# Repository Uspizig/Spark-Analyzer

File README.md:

# Spark Analyzer: The Programmable USB-C Power Delivery Analyzer & Power Supply

This is a modification of Spark Analyser to my personal needs. Please check the original Product here [now](https://www.crowdsupply.com/elektrothing/spark-analyzer).

The **Spark Analyzer** excels in power management. It is a versatile ESP32-powered device tailored for enhancing project development and debugging processes. It is fully compatible with USB-C Power Delivery (PD) and also supports the Programmable Power Supply (PPS) feature, allowing for precise control and management of power. Its compact design facilitates easy inline integration with existing setups, providing essential insights and control over power delivery.

Equipped with WiFi and BLE, the Spark Analyzer offers wireless connectivity, enabling developers to remotely monitor and adjust voltage levels, log data, and analyze power consumption through a user-friendly interface. This design prioritizes convenience and efficiency, removing the need for physical buttons and supporting distance operation.

## Features:

1. **Configure USB Power Delivery PD**: When the Spark Analyzer is connected to a USB port that supports Power Delivery (PD), you can configure the output voltage as 5V, 9V, 15V or 20V.

2. **Configure USB Programmable Power Supply PPS**: When the Spark Analyzer is connected to a USB port that supports Programmable Power Supply (PPS), then you can configure the output voltage between 3.3V and 21V in steps of 20 mV. You can also limit the current up to 3A in steps of 50mA.

3. **Power Analysis**: The Spark Analyzer comes with a current sensor. This allows for accurate current draw measurements, essential for understanding power usage in your projects.

4. **Wireless Control**: Untehther your development process with the Spark Analyzer’s wireless capabilities. With both WiFi and BLE, this tool allows remote control and data logging. Users can adjust settings and monitor data from a distance, offering a more flexible development experience.

5. **Open Source & Programmable**: As an open-source device, the Spark Analyzer offers unmatched versatility. It is fully programmable, allowing you to tailor its functionality to your specific applications. This customization extends to software and hardware, opening up endless possibilities for creative and efficient project development.

6. **Compact Design**: Designed for convenience, the Spark Analyzer's compact and sleek form factor allows for seamless integration into existing setups. Its compatibility with USB PD power sources and inline integration capability minimizes the need for additional equipment or extensive redesign, making it a versatile and user-friendly addition to any development environment.

5. **Safety**: Safety is crucial when working with electricity and is at the heart of Spark Analyzer. An integrated output FET allows for software programmable current limit that switches off the power in high-current scenarios.

6. **Data Storage**: Store your Voltage Curves on SD Card and play back voltage ramps

7. **Display**: Monitor live the current status of the Voltage Source

8. **RTC**: Operate the Device in remote areas without Wifi in Standalone mode and still have a proper Time Monitoring

9. **Air Quality**: Measure the Air Qulity with the BME680, BME688 or BME690: Temperature, Humidity, Pressure and eCO² to take actions based on Enviromental Data

10. **Gyro, ACC**: Identify Movement of the Device and take actions.

## Specifications

#### Power
- **Negotiable Power Delivery**: Options of 5 VDC, 9 VDC, 12 VDC, 15 VDC, 20 VDC; max 5 A (100 W at 20 VDC). It is also PPS compatible up to 21 VDC. Note: the Spark Analyzer comes preinstalled with firmware that supports PD. If you want to use PPS you can load this version instead: [WebApp_PPS](https://github.com/tooyipjee/Spark-Analyzer/tree/master/PlatformIO/WebApp_PPS).
- **USB Type-C Port**: For power delivery and integrated JTAG programming.
- **ON Semiconductor [FUSB302MPX](https://www.onsemi.com/pdf/datasheet/fusb302b-d.pdf)**: Programmable USB Type-C control and USB PD communication.
- **ESD Protection**: On D+/D-/CC1/CC2 pins.
- **Texas Instruments [TPS62175DQCT](https://www.ti.com/product/TPS62175/part-details/TPS62175DQCT)**: 3.3 VDC 0.5 A max output DC-DC Step-Down Converter.
- **Power Output**: 3.5 mm, 2-position terminal block.

#### I/O Configuration
- **GPIOs**: 4 GPIOs (I2C, UART, SPI compatible).
- **Power Pins**: 1x 5 VDC and 1x GND.

#### Microcontroller
- **Model**: [ESP32-S3 Wroom](https://www.espressif.com/sites/default/files/documentation/esp32-s3-wroom-1_wroom-1u_datasheet_en.pdf) 
- **Wi-Fi**: 802.11b/g/n.
- **Bluetooth**: BLE 4.2.
- **Flash Memory**: 4 MB.

#### Interface
- **3x LED Indicators**
  - Power On
  - Output Enable
  - Programmable LED/Debug
  - 2 x WS2812-4020 RGB Edge LED
- **Display**
  - GCA9a01 240x240 round Display
  - Backlight can be operated seperatly
- **Buttons**
  - Reset
  - Programmable 2Buttons/Debug
  - Jog Dial
- **Sensors**
  - LSM6 Gyro
  - RV3028 RTC Ultra Low Power
  - 4 GPIOs(3V3 logic) for operating outputs or read out Tacho Signals of FANs
  - BME280 (optional)
  - BME680 (optional) or - BME688 (optional) or - BME690 (optional)
- **Audio Amplifier**
  - MAX983657 AMP for Loudspeaker

#### Programming
- **RX/TX Pins**: For programming.
- **Micro SD Card**: For recall configuration files.
- **USB-C**: Built-in USB JTAG programmer (ESP32-S3), compatible with Arduino. Select ESP32-S3 Dev Board.

#### Output
- **Current Output**: [CC6904SO-10A](https://datasheet.lcsc.com/lcsc/2304140030_Cross-chip-CC6904SO-10A_C469389.pdf).
- **Current Sensor**: Hall Effect Current Sensor.
- **Output Enable**: [DMP3017SFG-7 FET](https://www.diodes.com/assets/Datasheets/products_inactive_data/DMP3017SFG.pdf).

## Spark Analyzer Mobile App

> **Note**: The Spark Analyzer Mobile App is currently in active development. The features described below are subject to change as we continue to improve the app.

The Spark Analyzer Mobile App, currently done for [Android](https://play.google.com/store/apps/details?id=com.elektrothing.SparkAnalyzer&hl=en&gl=US) (iOS support is available via [RemoteXY](https://apps.apple.com/us/app/remotexy/id1168130280), is the perfect companion to your Spark Analyzer device. It simplifies monitoring and controlling power delivery with these key features:

- **Voltage Selector**: Easily choose from different voltage levels (5 VDC, 9 VDC, 15 VDC, or 20 VDC) using a user-friendly selector.
- **Output Toggle**: Turn the power output on or off conveniently with a toggle switch.
- **Current Logging**: Save current draw as a .csv file.
- **Current Limit**: Ability to set a software current trip as a safety feature.
- **Read-time Display**: View current set point, current draw and output enable in real time on your phone.

### Key Features:

- **Voltage Selector**: The app comes with a user-friendly voltage selector that allows you to easily choose from the different voltage levels supported by the UCPD protocol. Whether you need 5V, 9V, 15V, or 20V, switching between these options is just a tap away.

- **Output Toggle**: Need to turn the power output on or off? The app features a convenient toggle switch that gives you full control over the Spark Analyzer's output, making it simple to manage your device remotely.

- **Current Draw Chart**: Keep an eye on your project's power consumption with the app's real-time current draw chart. This feature provides a graphical representation of the current being drawn, helping you to monitor and optimize your power usage effectively.

### Future Developments:

The Spark Analyzer Mobile App is continuously being improved, with several new features in the pipeline. Upcoming updates will include the ability to export logs for further analysis, set current limits to prevent overcurrent scenarios, and much more.

## Testing for Performance

At the heart of Spark Analyzer's design is a commitment to reliability and performance. To ensure that Spark Analyzer stands up to real-world demands, we subjected it to testing under use conditions.

### Max Current Test: 3A at 9V
Under a load condition of 3A at 9V, Spark Analyzer showcased its robust power delivery capabilities without any hitches.

### Max Voltage Test: 1.5A at 20V
Even at its maximum voltage output of 20V with a 1.5A load, Spark Analyzer continued to perform seamlessly, demonstrating its versatility and reliability.

## License

MIT License

Copyright (c) 2023 elektroThing

Permission is hereby granted, free of charge, to any person obtaining a copy
of this software and associated documentation files (the "Software"), to deal
in the Software without restriction, including without limitation the rights
to use, copy, modify, merge, publish, distribute, sublicense, and/or sell
copies of the Software, and to permit persons to whom the Software is
furnished to do so, subject to the following conditions:

The above copyright notice and this permission notice shall be included in all
copies or substantial portions of the Software.

THE SOFTWARE IS PROVIDED "AS IS", WITHOUT WARRANTY OF ANY KIND, EXPRESS OR
IMPLIED, INCLUDING BUT NOT LIMITED TO THE WARRANTIES OF MERCHANTABILITY,
FITNESS FOR A PARTICULAR PURPOSE AND NONINFRINGEMENT. IN NO EVENT SHALL THE
AUTHORS OR COPYRIGHT HOLDERS BE LIABLE FOR ANY CLAIM, DAMAGES OR OTHER
LIABILITY, WHETHER IN AN ACTION OF CONTRACT, TORT OR OTHERWISE, ARISING FROM,
OUT OF OR IN CONNECTION WITH THE SOFTWARE OR THE USE OR OTHER DEALINGS IN THE
SOFTWARE.

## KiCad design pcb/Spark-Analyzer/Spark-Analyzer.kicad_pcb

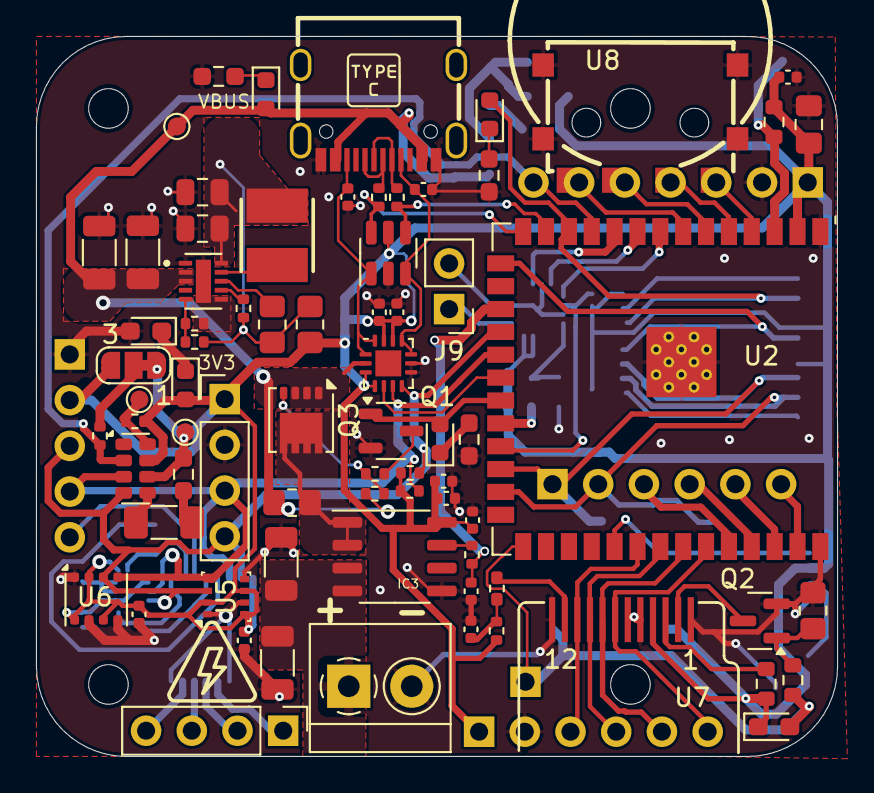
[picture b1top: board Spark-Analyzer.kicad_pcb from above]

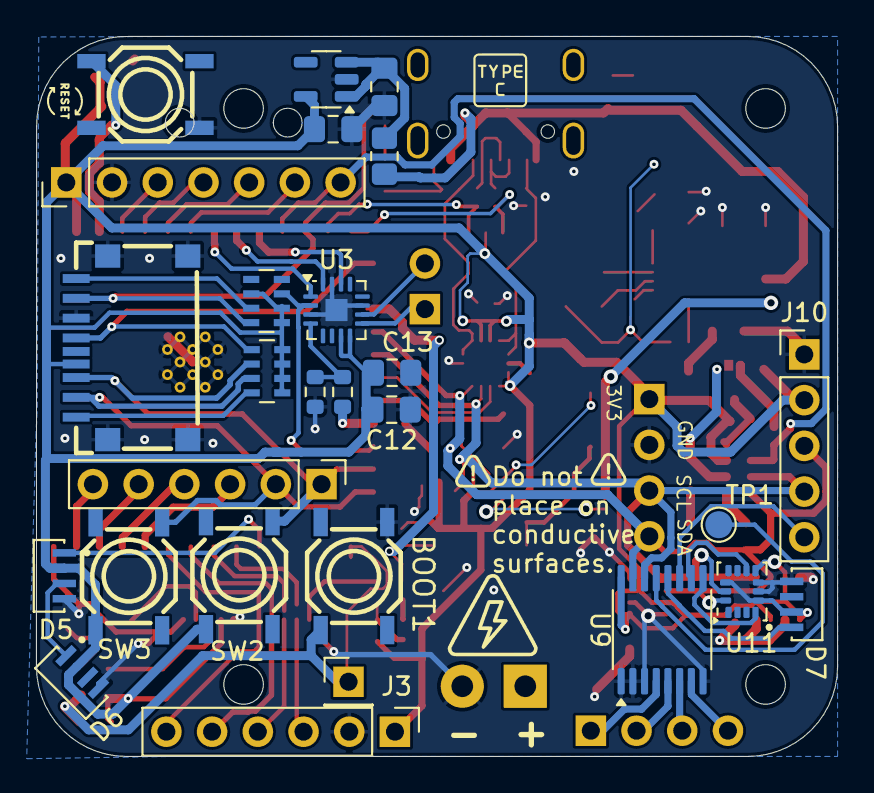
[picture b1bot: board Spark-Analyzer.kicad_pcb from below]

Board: 4 copper layers, 44.5 x 40.0 mm, 107 parts (28 on the bottom side), 78 nets.

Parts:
 : LOGO; highVoltage
 #2: LOGO; highVoltage
BOOT1: SW_Push; SW-SMD_4P-CORR-L5.2-W5.2-P3.70-LS6.4
C1, C20, C21, C22: 10u_1206; C_1206_3216Metric
C2: 22u; C_0805_2012Metric
C3: 10u; C_0805_2012Metric
C4, C5: 100p; C_0402_1005Metric
C6, C7, C8, C9, C11, C14, C15, C16, C24, C25: 100nF; C_0402_1005Metric
C10, C12, C13: 1uF; C_0805_2012Metric_Pad1.18x1.45mm_HandSolder
C17, C18: 4.7uF50V; C_0805_2012Metric_Pad1.18x1.45mm_HandSolder
C19: 220uF; C_1206_3216Metric_Pad1.33x1.80mm_HandSolder
D1, D2, D4: Green_0603; LED_0603_1608Metric
D3: Yellow_0603; LED_0603_1608Metric
D5, D6, D7: WS2812B-4020; LED_WS2812B-4020
H1, H2, H3, H4: MountingHole; MountingHole_2.2mm_M2
IC2: FUSB302MPX; WQFN-14-1EP_2.5x2.5mm_P0.5mm_EP1.45x1.45mm
IC3: CC6904SO-10A; SOP-8_3.9x4.9mm_P1.27mm
IC4: TPS62175DQCT; SON50P300X200X80-11N
J1: GT-USB-7010; USB-C_SMD-TYPE-C-31-M-12
J3, J12: Conn_01x06_Pin; PinHeader_1x06_P2.54mm_Vertical
J4, J7: Conn_01x04; PinHeader_1x04_P2.54mm_Vertical
J5: Conn_01x01; PinHeader_1x01_P2.54mm_Vertical
J6: Micro_SD_Card_Det_US; TF-SMD_XKTF-0803-0
J8: Conn_01x07_Pin; PinHeader_1x07_P2.54mm_Vertical
J9: Conn_01x02_Pin; PinHeader_1x02_P2.54mm_Vertical
J10: Conn_01x05; PinHeader_1x05_P2.54mm_Vertical
J11: KF350-3.5-2P; TerminalBlock_4Ucon_1x02_P3.50mm_Horizontal
JP1: SolderJumper_3_Bridged12; SolderJumper-3_P1.3mm_Bridged12_RoundedPad1.0x1.5mm_NumberL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
L1: 10uH; INDPM4040X300N
Q1: DTC143ECA-TP; SOT-23-3
Q2: 2N7002; SOT-23
Q3: DMP3017SFG-7; Diodes_PowerDI3333-8
R1: 100k; R_0402_1005Metric
R2: 1M2; R_0402_1005Metric
R3: 383k; R_0402_1005Metric
R4, R5: 0; R_0805_2012Metric_Pad1.20x1.40mm_HandSolder
R6, R7: 22; R_0402_1005Metric
R8: 100; R_0402_1005Metric
R9, R16: 2.7k; LED_0603_1608Metric_Pad1.05x0.95mm_HandSolder
R10, R12: 10k; R_0603_1608Metric
R11: 1M; R_0805_2012Metric_Pad1.20x1.40mm_HandSolder
R13, R14, R19, R24: 10k; R_0402_1005Metric
R15: 0R; R_0402_1005Metric_Pad0.72x0.64mm_HandSolder
R17, R18, R22: 2.7k; R_0603_1608Metric_Pad0.98x0.95mm_HandSolder
R20: 1k; R_0402_1005Metric
R21: DNF_0805; R_0805_2012Metric_Pad1.20x1.40mm_HandSolder
R23: 22; R_0603_1608Metric
R25: N.C.; R_0603_1608Metric
R26: 300K; R_0603_1608Metric
R27, R29: 10K; R_0402_1005Metric
R28: 0R; R_0805_2012Metric_Pad1.20x1.40mm_HandSolder
R30: 300R; R_0603_1608Metric_Pad0.98x0.95mm_HandSolder
RES1: SW_Push; SW-SMD_4P-CORR-L5.2-W5.2-P3.70-LS6.4
RN2, RN3: R_Pack04_Split; R_Array_Concave_4x0603
SW2, SW3: SW_Push; SW-SMD_4P-CORR-L5.2-W5.2-P3.70-LS6.4
TP1: TestPoint; TestPoint_Pad_D1.5mm
TP2, TP3, TP4: TestPoint; TestPoint_Pad_D1.0mm
U1: SRV05-4; SOT-23-6
U2: ESP32-S3-WROOM-1
U3: MAX98357A; TQFN-16-1EP_3x3mm_P0.5mm_EP1.23x1.23mm
U4: RV3032; MicroCrystal_C7_SON-8_1.5x3.2mm_P0.9mm
U5: BME280; Bosch_LGA-8_2.5x2.5mm_P0.65mm_ClockwisePinNumbering
U6: BME680; Bosch_LGA-8_3x3mm_P0.8mm_ClockwisePinNumbering
U7: GC9A01_IPS_display; GC9A01_IPS_display_reversed
U8: SIQ-02FVS3; SW-SMD_SIQ-02FVS3_1
U9: TCA9554PW; TSSOP-16_4.4x5mm_P0.65mm
U10: RT9013; SOT-23-5
U11: LSM6DSL; LGA-14_3x2.5mm_P0.5mm_LayoutBorder3x4y

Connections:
+3V3: C6.2, C7.1, C9.1, C10.1, C12.2, C13.1, C14.2, C15.1, C16.1, C18.2, C24.2, C25.2, D1.2 (A), D5.2 (VDD), D6.2 (VDD), D7.2 (VDD), IC2.3 (VDD_1), IC2.4 (VDD_2), IC2.12 (VCONN_1), IC2.13 (VCONN_2), IC3.8 (VCC), J3.1, J6.4 (VDD), J7.1, J8.1, J10.2, JP1.3 (B), R4.2, R9.1, R12.1, R13.1, R14.1, R23.1, R24.1, R29.2, RN2.1 (R1.1), RN2.2 (R2.1), RN2.6 (R3.2), RN3.5 (R4.2), RN3.6 (R3.2), RN3.7 (R2.2), RN3.8 (R1.2), SW2.2, SW3.2, U1.5 (VP), U2.2 (3V3), U3.7 (VDD), U3.8 (VDD), U4.7 (VDD), U5.2 (CSB), U5.6 (VDDIO), U5.8 (VDD), U6.2 (CSB), U6.6 (VDDIO), U6.8 (VDD), U7.4 (VDD), U9.16 (VDD), U10.5 (VOUT), U11.5 (VDDIO), U11.8 (VDD), U11.12 (CS)
/Current Sensor + Output Control/BSST: IC3.1 (IP+), IC3.2 (IP+), Q3.5 (D_1), R21.2
/Current Sensor + Output Control/OUTPUT_EN: D3.2 (A), Q1.1, U2.21 (GPIO13/TOUCH13/ADC2_CH2/FSPIQ/FSPIIO7/S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)
/Current Sensor + Output Control/VOUT: C1.1, C22.1, IC3.3 (IP-), IC3.4 (IP-), J11.1
/Current Sensor + Output Control/V_CURRENT: C8.1, R8.2, U2.17 (GPIO9/TOUCH9/ADC1_CH8/FSPIHD/SUBSPIHD)
/Microcontroller/AUDIO_CLK: U2.9 (GPIO16/U0CTS/ADC2_CH5/XTAL_32K_NH5), U3.16 (BCLK)
/Microcontroller/AUDIO_DAT: U2.8 (GPIO15/U0RTS/ADC2_CH4/XTAL_32K_P), U3.1 (DIN)
/Microcontroller/AUDIO_GAIN: RN2.3 (R3.1), U2.23 (GPIO21), U3.2 (GAIN_SLOT)
/Microcontroller/AUDIO_LR: U2.10 (GPIO17/U1TXD/ADC2_CH6), U3.14 (LRCLK)
/Microcontroller/AUDIO_SD: R26.2, U2.22 (GPIO14/TOUCH14/ADC2_CH3/FSPIWP/FSPIDQS/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)
/Microcontroller/BLK: BOOT1.2, J5.1, R9.2, R10.2, U2.27 (GPIO0/BOOT)
/Microcontroller/CMD: J6.3 (CMD), J12.1, RN3.2 (R2.1), SW2.1, U2.24 (GPIO47/SPICLK_P/SUBSPICLK_P_DIFF)
/Microcontroller/DAT0: D4.2 (A), J6.7 (DAT0), RN2.8 (R1.2), U2.12 (GPIO8/TOUCH8/ADC1_CH7/SUBSPICS1)
/Microcontroller/DAT1: J6.8 (DAT1), RN2.7 (R2.2)
/Microcontroller/DAT3: J6.2 (DAT3/CD), J12.2, RN3.3 (R3.1), SW3.1, U2.25 (GPIO48/SPICLK_N/SUBSPICLK_N_DIFF)
/Microcontroller/EN: R12.2, RES1.1, U2.3 (EN)
/Microcontroller/GPIO1: J12.6, U2.39 (GPIO1/TOUCH1/ADC1_CH0)
/Microcontroller/GPIO2: J12.5, U2.38 (GPIO2/TOUCH2/ADC1_CH1)
/Microcontroller/GPIO4: J8.3, U2.4 (GPIO4/TOUCH4/ADC1_CH3), U8.B
/Microcontroller/GPIO5: J8.4, U2.5 (GPIO5/TOUCH5/ADC1_CH4), U8.C
/Microcontroller/GPIO6: J8.5, U2.6 (GPIO6/TOUCH6/ADC1_CH5), U8.S
/Microcontroller/GPIO7: J8.6, U2.7 (GPIO7/TOUCH7/ADC1_CH6), U8.A
/Microcontroller/GPIO38: D5.1 (DIN), U2.31 (GPIO38/FSPIWP/SUBSPIWP)
/Microcontroller/INT1: U9.9 (P4), U11.4 (INT1)
/Microcontroller/INT2: U9.10 (P5), U11.9 (INT2)
/Microcontroller/INT_N: IC2.5 (INT_N), U2.20 (GPIO12/TOUCH11/ADC2_CH0/FSPICS0/FSPIIO4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)
/Microcontroller/LEDK: Q2.3 (D), U7.2 (LEDK)
/Microcontroller/LED_DIS: R23.2, U7.3 (LEDA)
/Microcontroller/MOSI: J3.3, U2.32 (MTCK/GPIO39/CLK_OUT3/SUBSPICS1), U7.10 (SDI)
/Microcontroller/RES_DIS: R15.1, U7.11 (~RESET)
/Microcontroller/RV3028_Int: J8.7, R27.2, U2.11 (GPIO18/U1RXD/ADC2_CH7/CLK_OUT3), U4.2 (INT)
/Microcontroller/SCK: J3.4, U2.33 (MTDO/GPIO40/CLK_OUT2), U7.9 (SCK)
/Microcontroller/SCL: IC2.6 (SCL), J7.3, J10.4, R14.2, U2.19 (GPIO11/TOUCH11/ADC2_CH0/FSPICS0/FSPIIO4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), U4.3 (SCL), U5.4 (SCK), U6.4 (SCK), U9.14 (SCL), U11.13 (SCL)
/Microcontroller/SDA: IC2.7 (SDA), J7.4, J10.3, R13.2, U2.18 (GPIO10/TOUCH10/ADC1_CH9/FSPICS0/FSPIIO4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), U4.4 (SDA), U5.3 (SDI), U6.3 (SDI), U9.15 (SDA), U11.14 (SDA)
/Microcontroller/SDCK: J6.5 (CLK), RN3.1 (R1.1), U2.15 (GPIO3/TOUCH3/ADC1_CH2)
/Microcontroller/SQW: J10.5, U9.11 (P6)
/Microcontroller/TFT_CS: J3.5, U2.34 (MTDI/GPIO41/CLK_OUT1), U7.8 (~CS)
/Microcontroller/TFT_DC: J3.6, U2.35 (MTMS/GPIO42), U7.7 (D/C)
/Microcontroller/U0RXD: J12.3, U2.36 (U0RXD/GPIO44/CLK_OUT2)
/Microcontroller/U0TXD: J12.4, U2.37 (U0TXD/GPIO43/CLK_OUT1)
/Microcontroller/USB_DN: R6.2, U1.4 (IO3), U2.13 (GPIO19/U1RTS/ADC2_CH8/CLK_OUT2/USB_D-)
/Microcontroller/USB_DP: R7.1, U1.6 (IO4), U2.14 (GPIO20/U1CTS/ADC2_CH9/CLK_OUT1/USB_D+)
GND: BOOT1.1, C1.2, C2.2, C3.2, C4.2, C5.2, C6.1, C7.2, C8.2, C9.2, C10.2, C11.2, C12.1, C13.2, C14.1, C15.2, C16.2, C17.1, C18.1, C19.2, C20.2, C21.2, C22.2, C24.1, C25.1, D5.4 (VSS), D6.4 (VSS), D7.4 (VSS), IC2.8 (GND_1), IC2.9 (GND_2), IC3.5 (GND), IC4.1 (PGND), IC4.6 (AGND), IC4.11 (EP), J1.A1 (GND), J1.A12 (GND), J1.B1 (GND), J1.B12 (GND), J3.2, J6.6 (VSS), J6.10 (SHELL), J6.11 (SHELL), J6.12 (SHELL), J6.13 (SHELL), J7.2, J8.2, J10.1, J11.2, Q1.2, Q2.2 (S), R3.2, R11.1, R16.2, R17.2, R18.2, R22.2, R25.1, RES1.2, U1.2 (VN), U2.1 (GND), U2.40 (GND), U2.41 (GND), U3.3 (GND), U3.11 (GND), U3.15 (GND), U3.17 (PAD), U4.5 (GND), U5.1 (GND), U5.5 (SDO), U5.7 (GND), U6.1 (GND), U6.5 (SDO), U6.7 (GND), U7.1 (GND), U7.5 (GND), U7.6 (GND), U7.12 (GND), U8.1 (EH), U8.2 (EH), U8.5 (EH), U8.6 (EH), U9.1 (A0), U9.2 (A1), U9.3 (A2), U9.8 (GND), U10.2 (GND), U11.6 (GND), U11.7 (GND)
unnamed: C11.1, R15.2, R24.2
unnamed: C19.1, R30.1
unnamed: D1.1 (K), R16.1
unnamed: D2.1 (K), R17.1
unnamed: D3.1 (K), R18.1
unnamed: D4.1 (K), R22.1
unnamed: D5.3 (DOUT), D6.1 (DIN)
unnamed: D7.1 (DIN), U9.12 (P7)
unnamed: C5.1, IC2.10 (CC1_1), IC2.11 (CC1_2), J1.A5 (CC1), U1.3 (IO2)
unnamed: C4.1, IC2.1 (CC2_1), IC2.14 (CC2_2), J1.B5 (CC2), U1.1 (IO1)
unnamed: IC3.7 (OUT), R8.1
unnamed: IC4.5 (FB), R2.2, R3.1
unnamed: IC4.7 (PG), R1.2
unnamed: IC4.8 (SLEEP), R5.1
unnamed: IC4.9 (SW), L1.1
unnamed: C2.1, C3.1, IC4.10 (VOS), L1.2, R1.1, R2.1, R4.1, R5.2
unnamed: J1.A6 (D+), J1.B6 (D+), R7.2
unnamed: J1.A7 (D-), J1.B7 (D-), R6.1
unnamed: J4.1, U9.4 (P0)
unnamed: J4.2, U9.5 (P1)
unnamed: J4.3, U9.6 (P2)
unnamed: J4.4, U9.7 (P3)
unnamed: J6.1 (DAT2), RN3.4 (R4.1)
unnamed: J9.1, U3.9 (OUTP)
unnamed: J9.2, U3.10 (OUTN)
unnamed: JP1.2 (C), R27.1
unnamed: Q1.3, R20.2
unnamed: Q2.1 (G), R10.1, R11.2
unnamed: Q3.4 (G), R19.2, R20.1
unnamed: R25.2, R26.1, U3.4 (~SD_MODE)
unnamed: R29.1, TP2.1, U4.8 (EVI)
unnamed: TP1.1, U9.13 (~INT)
unnamed: C17.2, R28.1, U10.1 (VIN), U10.3 (EN)
VBUS: C20.1, C21.1, D2.2 (A), IC2.2 (VBUS), IC4.2 (VIN), IC4.3 (EN), J1.A4 (VBUS), J1.A9 (VBUS), J1.B4 (VBUS), J1.B9 (VBUS), Q3.1, Q3.2, Q3.3, R19.1, R21.1, R28.2, TP4.1
VPP: JP1.1 (A), R30.2, TP3.1, U4.6 (V_BCU)

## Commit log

2025-01-02 Changes Outline
    Make it easier to produce
2025-01-02 Add files via upload
    - Replaced ESP 32 C3 with ESP32-S3 Wroom
    - Added GC9a01 Display
    - Added Micro SD Card Reader
    - Added RV3028 RTC
    - Added Audio Amplifier MAX98357
    - Added BME680 Air Quality Analyser
2025-01-02 Update README.md
    Changed to new Design
2025-01-02 Update README.md
    fixed typos
2025-04-13 Update README.md
    Details
